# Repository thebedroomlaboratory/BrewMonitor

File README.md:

# BrewMonitor

## The Arduino and Cloud-based homebrewing controller

Homepage: http://thebedlab.com/brewmonitor-the-arduino-and-cloud-based-homebrewing-controller/

Demo sites:

* http://dev.thebedlab.com/~martin/brewmonitor/ (PHP - Stable)
* http://dev.thebedlab.com/brewmonitor/ (Node - Unstable)

### Arduino Library Requirements (latest versions):

* http://www.pjrc.com/teensy/td_libs_OneWire.html
* http://milesburton.com/Main_Page?title=Dallas_Temperature_Control_Library

### REST API Format

* PHP Backend
  * http://dev.thebedlab.com/~martin/brewmonitor/api/help (to be added but this is a placeholder)
  * http://dev.thebedlab.com/~martin/brewmonitor/api/readings (GET)
  * http://dev.thebedlab.com/~martin/brewmonitor/api/readings (POST)
    * as URL parameters
    * `http://dev.thebedlab.com/~martin/brewmonitor/api/readings/?device=1&temp=20.0&heaton=1.0`
* Node.js Backend
  * http://dev.thebedlab.com/brewmonitor/api/v1.0/help
  * http://dev.thebedlab.com/brewmonitor/api/v1.0/list (GET)
    * URL parameters optional, e.g.
    * http://dev.thebedlab.com/brewmonitor/api/v1.0/list?devid=1&userid=1
  * http://dev.thebedlab.com/brewmonitor/api/v1.0 (POST)
    * `{ "userid": 0, "devid": 0, "temps": [{"sensid": 0, "temp": 20.2}, {"sensid": 1, "temp": 20.8}], "timestamp": "2014-11-15T16:56:08.506Z" }`

### Installation

First thing to do is to clone this repository. All paths are given relative to the root of the repository. From here on it is also assumed that the root of the repository will show up at http://domain/

#### Stable Version (PHP/MySQL Backend with Angular on frontend)

* Install apache2 mysql php5 php5-mcrypt php5-apache2 php5-zip php5-mysql php5-pdo-mysql phpmyadmin composer
* `composer self-update`
* `composer global require "laravel/installer=~1.1"`
* add ~/.composer/vendor/bin to $PATH in .bash_profile
* `cd Backend`
* `wget https://github.com/laravel/laravel/archive/master.zip`
* `rm -r laravel`
* `unzip master.zip`
* `mv laravel-master laravel`
* `cd laravel`
* `git checkout .`
* `composer install`
* `cd ../../Frontend/brewmonitor/js`
* `mkdir graphing`
* `cd graphing`
* `wget http://dev.thebedlab.com/~martin/brewmonitor/js/graphing/angular-moment.min.js; wget http://dev.thebedlab.com/~martin/brewmonitor/js/graphing/angular-moment.min.js.map; wget http://dev.thebedlab.com/~martin/brewmonitor/js/graphing/line-chart.min.js; wget http://dev.thebedlab.com/~martin/brewmonitor/js/graphing/moment.min.js`
* Configure your username/password settings in `Backend/laravel/app/config/database.php`
* Create database table and seed it with some sample data
  * Use phpmyadmin to create table called `brewmonitor`
  * `cd Backend/laravel`
  * `php artisan migrate`
  * `php artisan db:seed`
* That's it! You should now be able to see a graph in your browser at http://domain/Frontend/brewmonitor/ once apache2 and mysql are running

#### Development Version (Node.js/MongoDB Backend)

##### MongoDB

Make sure Mongo is installed and running. A dump of the DB was created in `Backend` using:
```bash
cd Backend
mongodump -d brew
```
This can be loaded locally using:
```bash
cd Backend
mongorestore
```

##### Node-Red

Download and extract node-red zip file from http://nodered.org/ to `Backend/node-red`
```bash
cd Backend/node-red
npm install --production
npm install mongodb
rm settings.js
ln -s ../settings.js
```
If you have any complications or want to install Additional Nodes, check the instructions on http://nodered.org/docs/getting-started/installation.html

##### Apache2 and Node-Red at same time

Configure Apache with the following settings:
```bash
LoadModule proxy_module modules/mod_proxy.so
LoadModule proxy_http_module modules/mod_proxy_http.so
LoadModule proxy_wstunnel_module modules/mod_proxy_wstunnel.so

ProxyPreserveHost On
ProxyRequests Off
ProxyPass /brewmonitor/comms ws://127.0.0.1:8123/brewmonitor/comms
ProxyPass /brewmonitor http://127.0.0.1:8123/brewmonitor
ProxyPassReverse /brewmonitor http://127.0.0.1:8123/brewmonitor
```
You can do this using:

* `a2enmod` and `/etc/apache2/sites-enabled/000-default.conf` (Ubuntu)
* Or all in your `httpd.conf` file by adding the text as above (codio.com)
* Either way, remember to restart Apache afterwards so that the settings can take effect
 
After that, check that your node-red app/server settings match up. This can be found in `Backend/settings.js`:

* `uiPort: 8123,`
* `httpRoot: '/brewmonitor',`

You may as well allow AJAX calls from other servers at this point too, if required (Ionic app for instance...)
```bash
 httpNodeCors: {
  origin: "*",
  methods: "GET,PUT,POST,DELETE"
 },
```

##### Running Server
Make sure MongoDB and Apache are running, then run the following command:
```bash
./startNodeRed.sh
```
This launches the Node-Red server which can then be found at http://domain/brewmonitor/. To run it as a daemon, do the following (sudo may be required for global npm install):
```bash
cd Backend/node-red
npm install forever -g
forever start red.js ../BrewMonitor.json
```

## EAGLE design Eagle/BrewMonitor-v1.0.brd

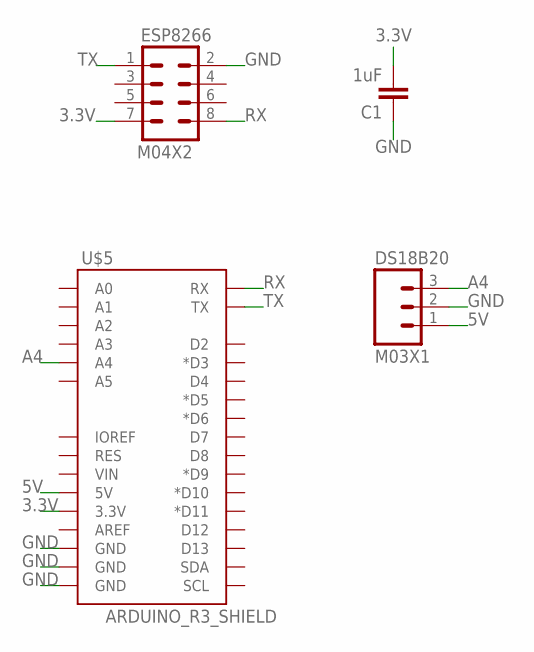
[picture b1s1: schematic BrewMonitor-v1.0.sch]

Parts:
C1: 1uF; CAP-PTH-SMALL
DS18B20: M03X1; SCREWTERMINAL-3.5MM-3
ESP8266: M04X2; 2X4
U$5: ARDUINO_R3_SHIELD; UNO_R3_SHIELD

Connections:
3.3V: C1.2, ESP8266.7, U$5.3.3V
5V: DS18B20.1, U$5.5V
A4: DS18B20.3, U$5.A4
GND: C1.1, DS18B20.2, ESP8266.2, U$5.GND@0 (GND), U$5.GND@1 (GND), U$5.GND@2 (GND)
RX: ESP8266.8, U$5.RX
TX: ESP8266.1, U$5.TX

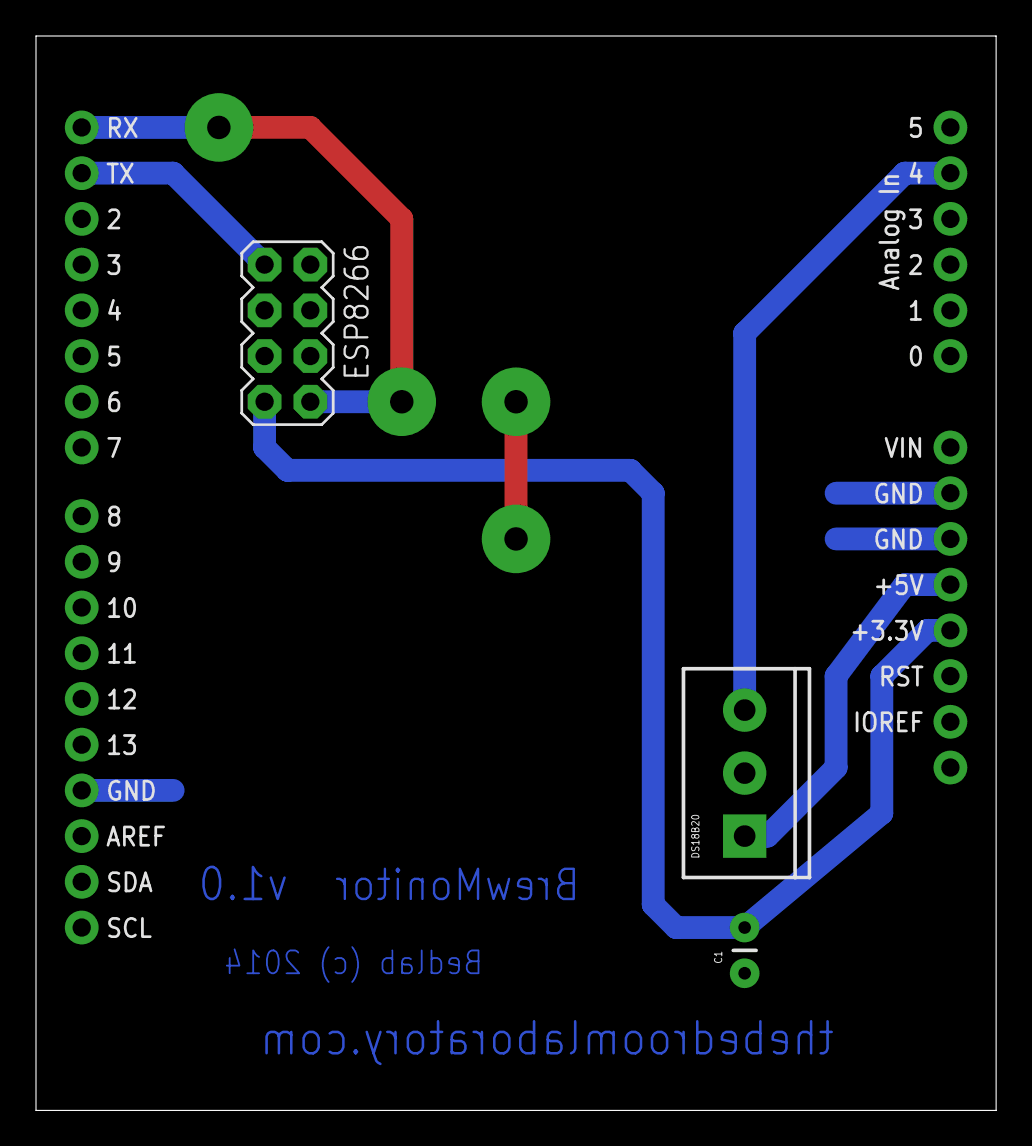
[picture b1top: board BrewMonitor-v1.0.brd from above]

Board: 2 copper layers, 53.3 x 59.7 mm, 4 parts (0 on the bottom side), 6 nets.

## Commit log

2014-10-02 Update LICENSE
2014-10-02 First commit of code/design files. The Arduino/BrewMonitor/BrewMonitor.ino sketch is working perfectly but could do with a bit of polishing and power-aware coding. The Eagle directory is currently on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
2014-10-07 Edited arduino sketch to remove all software serial references. Changed the frequency of temperature posts to 30 mins. This reduces the likelihood of stalling in the javascript on the front end as a 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
2014-10-08 Added laravel files for PHP backend.
2014-10-08 Added javascript libraries for Angular JS app. Angular page is in Laravel views directory.
2014-10-08 Fixing Database query format
2014-10-08 No need to have javascript libraries in repository
2014-10-08 and again
2014-10-11 Updated Eagle Schematic for the correct parts and made net connections. The brd file still needs updating.
2014-10-13 Updated Schematic and Board files. Circuit now complete.
2014-10-13 Removed file for placeholder circuit.
2014-10-28 Update BrewMonitor.ino
    Changed timing slightly to get better accuracy on 30min gap between reading submissions.
2014-11-02 Fixed a JavaScript typo
2014-11-12 Initial commit adding Node-Red Backend.
2014-11-12 Tidying Hardware folder structure.
2014-11-13 Hooked up API calls to MongoDB. API format described in README.md file.
2014-11-15 Backup of MongoDB, so that others can collaborate. Instructions for using this added to README.md.
2014-11-15 Tidying up directory structure.
2014-11-19 initial working Node-Express/Angular Port
2015-01-18 Updated code for first version of temperature controller with WiFi. Code needs to be tidied but is currently live on both the client and server and it's hooked up to two two different IPAs fermenting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
2015-01-18 Updated database migration file for new schema.
2015-01-19 Tidied up python script a bit for better management of DB
2015-01-21 Removed some unnecessary spacing at page top.
2015-01-26 Update README.md
    Extended ReadMe with branch-specific info and how to configure Apache2 and Node-Red to work together
2015-01-26 Updated code for Coexistance with Apache2. Moved BrewMonitor.js to .json file.
2015-01-26 Fixed minor path errors in URL routing and its description in README.md
2015-01-26 Updated node-red app so that it doesn't print to console any more. Debug tab in browser is enough
2015-01-30 directory rearrangement, so that PHP backend structure fits better in the repository.
2015-01-30 updating laravel file to figure out installation procedure - Part 1
2015-01-30 getting rid of unnecessary laravel files so that the PHP backend can be installed easier.
2015-01-31 Nearly there with laravel fixing and path issues
2015-01-31 All paths fixed and process for installation fully documented in README.md
2015-01-31 Updated README.md to reflect current API routes
2015-01-31 Untracking .codio file because there's no need for it in repository.
2015-02-04 Added functionality for searching DB through API based on ID fields. Updated Readme and help file to reflect that.
2015-02-24 Intial
2015-02-24 added SuperCharged Todo list :fire:
2015-02-26 halfway to using new format
2015-03-01 using mongo data in demo.html
2015-03-04 post to add new readings
2015-03-04 adding logs to ignore file
2015-03-04 adding find to read from db for list method
2015-03-04 updating front end service
2017-02-05 Updated endpoints and fermentation temperature

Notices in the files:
Eagle/BrewMonitor-v1.0.brd:
Bedlab (c) 2014
parts and their libraries:
SparkFun-Passives: Licensing: Creative Commons ShareAlike 4.0 International - https://creativecommons.org/licenses/by-sa/4.0
